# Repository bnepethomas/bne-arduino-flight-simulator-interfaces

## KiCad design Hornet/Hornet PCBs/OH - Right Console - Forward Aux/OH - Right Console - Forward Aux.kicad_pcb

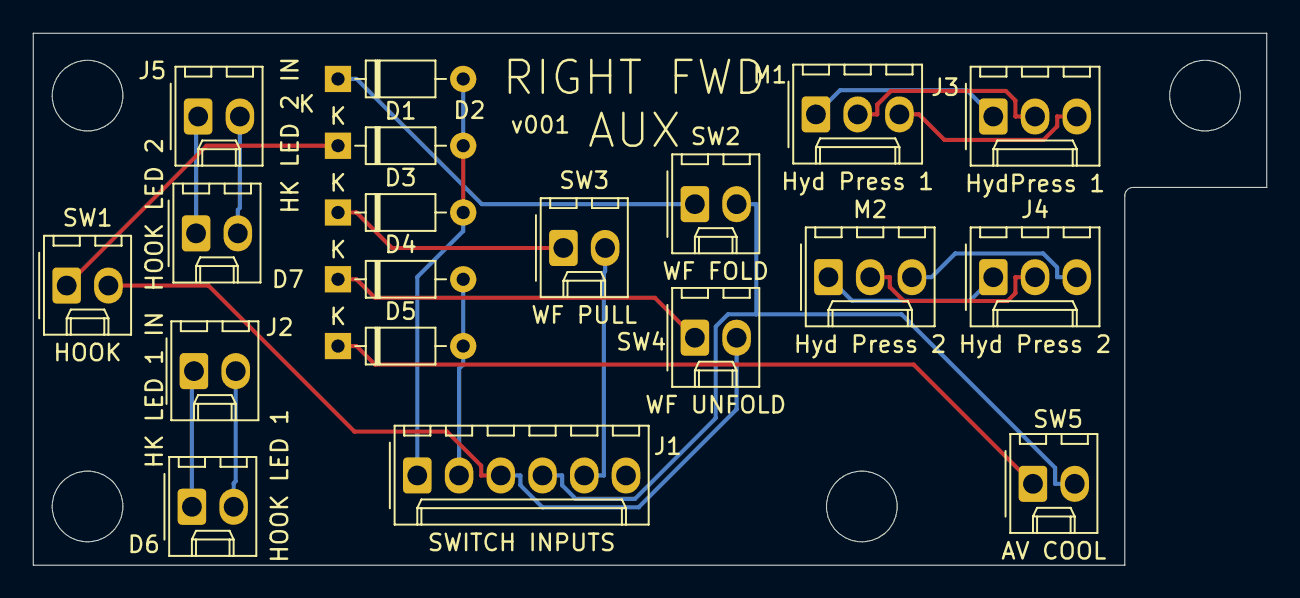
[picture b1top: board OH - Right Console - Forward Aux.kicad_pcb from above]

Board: 2 copper layers, 75.1 x 32.4 mm, 23 parts (0 on the bottom side), 20 nets.

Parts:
D1, D2, D3, D4, D5: D; D_Signal_P7.62mm_Horizontal
D6: HOOK LED 1; Molex_1x02_P2.54mm_Vertical
D7: HOOK LED 2; Molex_1x02_P2.54mm_Vertical
H1, H2, H3, H4: MountingHole; MountingHole_4.3mm_M4
J1: SWITCH INPUTS; Molex_1x06_P2.54mm_Vertical
J2: HK LED 1 IN; Molex_1x02_P2.54mm_Vertical
J3: HydPress 1; Molex_1x03_P2.54mm_Vertical
J4: Hyd Press 2; Molex_1x03_P2.54mm_Vertical
J5: HK LED 2 IN; Molex_1x02_P2.54mm_Vertical
M1: Hyd Press 1; Molex_1x03_P2.54mm_Vertical
M2: Hyd Press 2; Molex_1x03_P2.54mm_Vertical
SW1: HOOK; Molex_1x02_P2.54mm_Vertical
SW2: WF FOLD; Molex_1x02_P2.54mm_Vertical
SW3: WF PULL; Molex_1x02_P2.54mm_Vertical
SW4: WF UNFOLD; Molex_1x02_P2.54mm_Vertical
SW5: AV COOL; Molex_1x02_P2.54mm_Vertical

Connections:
/COL1: D1.2, D2.2, D3.2, J1.1
/COL2: D4.2, D5.2, J1.2
/ROW1: J1.3, SW1.2, SW4.2
/ROW2: J1.4, SW2.2, SW5.2
/ROW3: J1.5, SW3.2
unnamed: D1.1, SW1.1
unnamed: D2.1, SW2.1
unnamed: D3.1, SW3.1
unnamed: D4.1, SW4.1
unnamed: D5.1, SW5.1
unnamed: D6.1, J2.1
unnamed: D6.2, J2.2
unnamed: D7.1, J5.1
unnamed: D7.2, J5.2
unnamed: J3.1, M1.1
unnamed: J3.2, M1.2
unnamed: J3.3, M1.3
unnamed: J4.1, M2.1
unnamed: J4.2, M2.2
unnamed: J4.3, M2.3

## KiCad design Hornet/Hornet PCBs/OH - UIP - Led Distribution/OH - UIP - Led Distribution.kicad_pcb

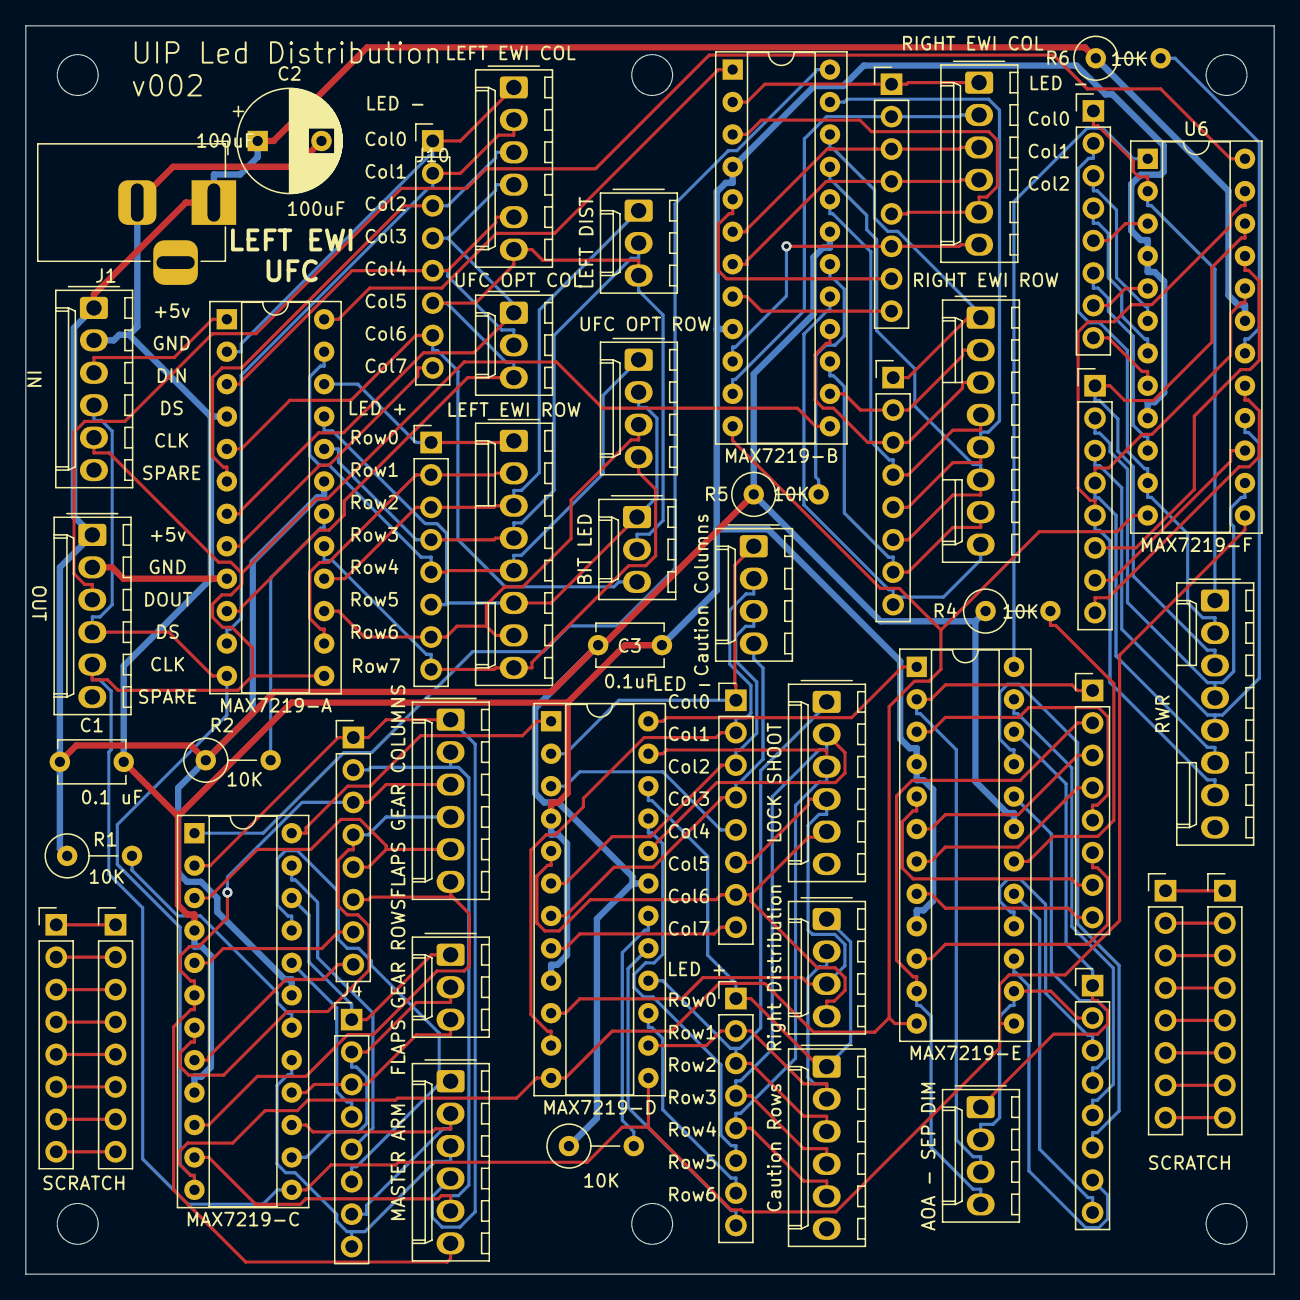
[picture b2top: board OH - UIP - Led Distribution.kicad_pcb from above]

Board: 2 copper layers, 97.8 x 97.8 mm, 57 parts (0 on the bottom side), 129 nets.

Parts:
C1, C3: 0.1uF; C_Disc_D5.1mm_W3.2mm_P5.00mm
C2: 100uF; CP_Radial_D8.0mm_P5.00mm
H1, H2, H3, H4, H5, H6: MountingHole; MountingHole_3.2mm_M3
J1: Conn_01x02_Female; BarrelJack_Horizontal
J2, J3: Molex_1x06_P2.54mm_Vertical
J4, J5, J9, J10, J16, J17, J23, J24, J26, J27, J30, J31, J32, J33, J35, J36: PinHeader_1x08_P2.54mm_Vertical
J6: FLAPS GEAR COLUMNS; Molex_1x06_P2.54mm_Vertical
J7: FLAPS GEAR ROWS; Molex_1x03_P2.54mm_Vertical
J8: MASTER ARM; Molex_1x06_P2.54mm_Vertical
J11: LEFT EWI ROW; Molex_1x08_P2.54mm_Vertical
J12: LEFT EWI COL; Molex_1x06_P2.54mm_Vertical
J13: UFC OPT COL; Molex_1x03_P2.54mm_Vertical
J14: UFC OPT ROW; Molex_1x04_P2.54mm_Vertical
J15: BIT LED; Molex_1x03_P2.54mm_Vertical
J18: Right Distribution; Molex_1x04_P2.54mm_Vertical
J19: LOCK SHOOT; Molex_1x06_P2.54mm_Vertical
J20: Caution Columns; Molex_1x04_P2.54mm_Vertical
J21: Caution Rows; Molex_1x06_P2.54mm_Vertical
J22: LEFT DIST; Molex_1x03_P2.54mm_Vertical
J25: AOA - SEP DIM; Molex_1x04_P2.54mm_Vertical
J28: RIGHT EWI ROW; Molex_1x08_P2.54mm_Vertical
J29: RIGHT EWI COL; Molex_1x06_P2.54mm_Vertical
J34: RWR; Molex_1x08_P2.54mm_Vertical
R1, R2, R3, R4, R5, R6: 10K; R_Axial_DIN0309_L9.0mm_D3.2mm_P5.08mm_Vertical
U1: MAX7219-C; DIP-24_W7.62mm_Socket
U2: MAX7219-A; DIP-24_W7.62mm_Socket
U3: MAX7219-D; DIP-24_W7.62mm_Socket
U4: MAX7219-E; DIP-24_W7.62mm_Socket
U5: MAX7219-B; DIP-24_W7.62mm_Socket
U6: MAX7219-F; DIP-24_W7.62mm_Socket

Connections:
+5V: C1.1, C2.1, C3.1, J1.1, J2.1, J3.1, R1.1, R2.1, R3.1, R4.1, R5.1, R6.1, U1.19, U2.19, U3.19, U4.19, U5.19, U6.19
/A-DOUT-B-DIN: U2.24, U5.1
/ACol0: J10.1, J12.1, U2.2
/ACol1: J10.2, J12.2, U2.11
/ACol2: J10.3, J12.3, U2.6
/ACol3: J10.4, J12.4, J13.1, U2.7
/ACol4: J10.5, J12.5, J13.2, U2.3
/ACol5: J10.6, J12.6, J13.3, J15.2, J22.3, U2.10
/ACol6: J10.7, J15.3, U2.5
/ACol7: J10.8, U2.8
/ARow0: J9.1, J11.1, U2.22
/ARow1: J9.2, J11.2, U2.14
/ARow2: J9.3, J11.3, J22.1, U2.16
/ARow3: J9.4, J11.4, J22.2, U2.20
/ARow4: J9.5, J11.5, J14.1, U2.23
/ARow5: J9.6, J11.6, J14.2, J15.1, U2.21
/ARow6: J9.7, J11.7, J14.3, U2.15
/ARow7: J9.8, J11.8, J14.4, U2.17
/B-DOUT-C-DIN: U1.1, U5.24
/BCol0: J27.1, J29.1, U5.2
/BCol1: J27.2, J29.2, U5.11
/BCol2: J27.3, J29.3, U5.6
/BCol3: J27.4, J29.4, U5.7
/BCol4: J27.5, J29.5, U5.3
/BCol5: J27.6, J29.6, U5.10
/BCol6: J27.7, U5.5
/BCol7: J27.8, U5.8
/BRow0: J26.1, J28.1, U5.22
/BRow1: J26.2, J28.2, U5.14
/BRow2: J26.3, J28.3, U5.16
/BRow3: J26.4, J28.4, U5.20
/BRow4: J26.5, J28.5, U5.23
/BRow5: J26.6, J28.6, U5.21
/BRow6: J26.7, J28.7, U5.15
/BRow7: J26.8, J28.8, U5.17
/C-DOUT-D-DIN: U1.24, U3.1
/CCol0: J5.1, J6.1, J8.4, U1.2
/CCol1: J5.2, J6.2, J8.5, U1.11
/CCol2: J5.3, J6.3, J8.6, U1.6
/CCol3: J5.4, J6.4, U1.7
/CCol4: J5.5, J6.5, U1.3
/CCol5: J5.6, J6.6, U1.10
/CCol6: J5.7, U1.5
/CCol7: J5.8, U1.8
/CLK: J2.5, J3.5, U1.13, U2.13, U3.13, U4.13, U5.13, U6.13
/CRow0: J4.1, J7.1, U1.22
/CRow1: J4.2, J7.2, U1.14
/CRow2: J4.3, J7.3, U1.16
/CRow3: J4.4, U1.20
/CRow4: J4.5, U1.23
/CRow5: J4.6, J8.1, U1.21
/CRow6: J4.7, J8.2, U1.15
/CRow7: J4.8, J8.3, U1.17
/D-DOUT-E-DIN: U3.24, U4.1
/DCol0: J16.1, J20.1, U3.2
/DCol1: J16.2, J20.2, U3.11
/DCol2: J16.3, J20.3, U3.6
/DCol3: J16.4, J20.4, U3.7
/DCol4: J16.5, U3.3
/DCol5: J16.6, J18.3, J19.4, U3.10
/DCol6: J16.7, J18.4, J19.5, U3.5
/DCol7: J16.8, U3.8
/DIN: J2.3, U2.1
/DOUT: J3.3, U6.24
/DRow0: J17.1, J18.1, J21.1, U3.22
/DRow1: J17.2, J18.2, J21.2, U3.14
/DRow2: J17.3, J19.1, J21.3, U3.16
/DRow3: J17.4, J19.2, J21.4, U3.20
/DRow4: J17.5, J19.3, J21.5, U3.23
/DRow5: J17.6, U3.21
/DRow6: J17.7, U3.15
/DRow7: J17.8, U3.17
/E-DOUT-F-DIN: U4.24, U6.1
/ECol0: J23.1, J25.3, U4.2
/ECol1: J23.2, J25.4, U4.11
/ECol2: J23.3, U4.6
/ECol3: J23.4, U4.7
/ECol4: J23.5, U4.3
/ECol5: J23.6, U4.10
/ECol6: J23.7, U4.5
/ECol7: J23.8, U4.8
/ERow0: J24.1, J25.1, U4.22
/ERow1: J24.2, J25.2, U4.14
/ERow2: J24.3, U4.16
/ERow3: J24.4, U4.20
/ERow4: J24.5, U4.23
/ERow5: J24.6, U4.21
/ERow6: J24.7, U4.15
/ERow7: J24.8, U4.17
/FCol0: J32.1, J34.1, U6.2
/FCol1: J32.2, J34.2, U6.11
/FCol2: J32.3, U6.6
/FCol3: J32.4, U6.7
/FCol4: J32.5, U6.3
/FCol5: J32.6, U6.10
/FCol6: J32.7, U6.5
/FCol7: J32.8, U6.8
/FRow0: J33.1, J34.3, U6.22
/FRow1: J33.2, J34.4, U6.14
/FRow2: J33.3, J34.5, U6.16
/FRow3: J33.4, J34.6, U6.20
/FRow4: J33.5, J34.7, U6.23
/FRow5: J33.6, U6.21
/FRow6: J33.7, U6.15
/FRow7: J33.8, U6.17
/LOAD: J2.4, J3.4, U1.12, U2.12, U3.12, U4.12, U5.12, U6.12
GND: C1.2, C2.2, C3.2, J1.2, J2.2, J3.2, U1.4, U1.9, U2.4, U2.9, U3.4, U3.9, U4.4, U4.9, U5.4, U5.9, U6.4, U6.9
unnamed: J30.1, J31.1
unnamed: J30.2, J31.2
unnamed: J30.3, J31.3
unnamed: J30.4, J31.4
unnamed: J30.5, J31.5
unnamed: J30.6, J31.6
unnamed: J30.7, J31.7
unnamed: J30.8, J31.8
unnamed: J35.1, J36.1
unnamed: J35.2, J36.2
unnamed: J35.3, J36.3
unnamed: J35.4, J36.4
unnamed: J35.5, J36.5
unnamed: J35.6, J36.6
unnamed: J35.7, J36.7
unnamed: J35.8, J36.8
unnamed: R1.2, U1.18
unnamed: R2.2, U2.18
unnamed: R3.2, U3.18
unnamed: R4.2, U4.18
unnamed: R5.2, U5.18
unnamed: R6.2, U6.18

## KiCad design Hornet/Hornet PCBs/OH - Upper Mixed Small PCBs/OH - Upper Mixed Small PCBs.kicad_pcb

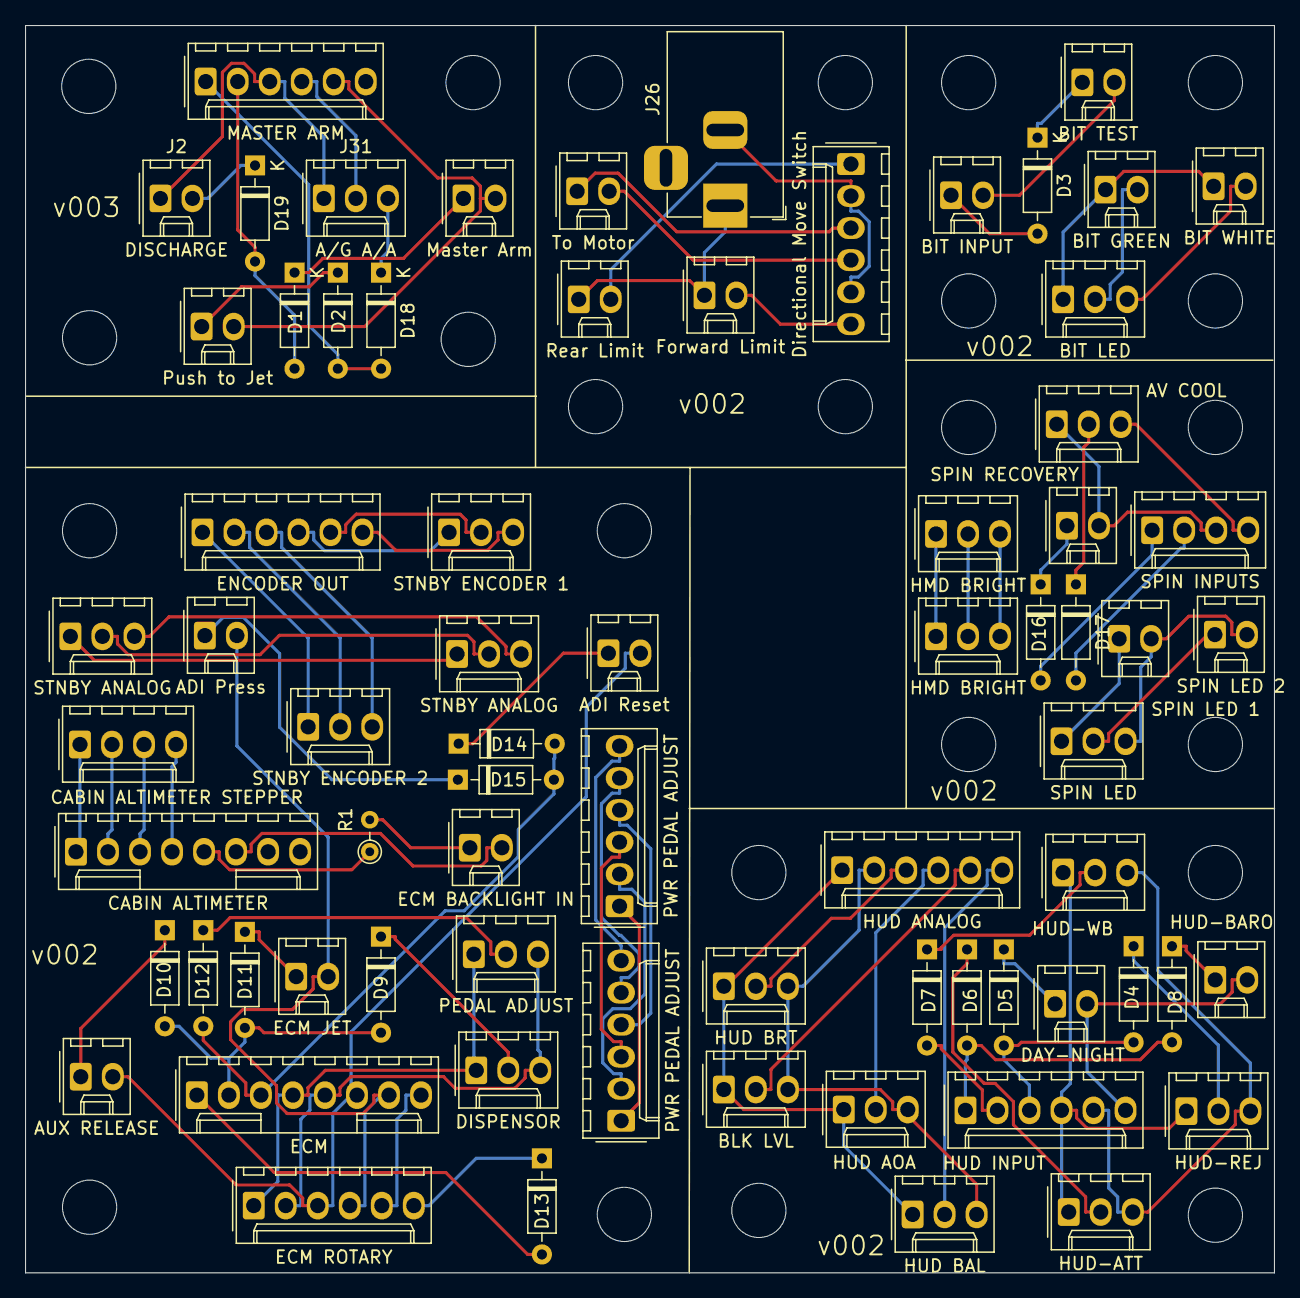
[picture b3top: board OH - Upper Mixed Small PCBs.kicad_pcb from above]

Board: 2 copper layers, 99.1 x 98.9 mm, 96 parts (0 on the bottom side), 87 nets.

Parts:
D1, D2, D3, D4, D5, D6, D7, D8, D9, D10, D11, D12, D13, D14, D15, D16, D17: D; D_Signal_P7.62mm_Horizontal
D18, D19: D; D_DO-35_SOD27_P7.62mm_Horizontal
H1, H5, H8, H11, H12, H14, H15, H16, H17, H18, H19, H20, H21, H22, H23, H24, H25, H26, H27, H28, H29, H30, H31, H32: MountingHole; MountingHole_4.3mm_M4
J1: HUD ANALOG; Molex_1x06_P2.54mm_Vertical
J2: DISCHARGE; Molex_KK-254_AE-6410-02A_1x02_P2.54mm_Vertical
J4: BIT GREEN; Molex_1x02_P2.54mm_Vertical
J5: BIT WHITE; Molex_1x02_P2.54mm_Vertical
J6: MASTER ARM; Molex_1x06_P2.54mm_Vertical
J7: BIT INPUT; Molex_1x02_P2.54mm_Vertical
J8: BIT LED; Molex_1x03_P2.54mm_Vertical
J9, J13: PWR PEDAL ADJUST; Molex_1x06_P2.54mm_Vertical
J10: HUD INPUT; Molex_1x06_P2.54mm_Vertical
J11: ECM BACKLIGHT IN; Molex_1x02_P2.54mm_Vertical
J12: CABIN ALTIMETER STEPPER; Molex_1x04_P2.54mm_Vertical
J14: CABIN ALTIMETER; Molex_1x08_P2.54mm_Vertical
J15, J19: STNBY ANALOG; Molex_1x03_P2.54mm_Vertical
J16: ECM; Molex_1x08_P2.54mm_Vertical
J17: STNBY ENCODER 1; Molex_1x03_P2.54mm_Vertical
J18: STNBY ENCODER 2; Molex_1x03_P2.54mm_Vertical
J20: ENCODER OUT; Molex_1x06_P2.54mm_Vertical
J21: SPIN INPUTS; Molex_1x04_P2.54mm_Vertical
J22: SPIN LED; Molex_1x03_P2.54mm_Vertical
J23: HMD BRIGHT; Molex_1x03_P2.54mm_Vertical
J24: SPIN LED 1; Molex_1x02_P2.54mm_Vertical
J25: SPIN LED 2; Molex_1x02_P2.54mm_Vertical
J26: PEDAL POWER IN; BarrelJack_Horizontal
J27: To Motor; Molex_1x02_P2.54mm_Vertical
J28: Rear Limit; Molex_1x02_P2.54mm_Vertical
J29: Directional Move Switch; Molex_1x06_P2.54mm_Vertical
J30: Forward Limit; Molex_1x02_P2.54mm_Vertical
J31: A/G A/A; Molex_KK-254_AE-6410-03A_1x03_P2.54mm_Vertical
R1: 1K; PT_R_Axial_DIN0204_L3.6mm_D1.6mm_P2.54mm_Vertical
RV1: HUD BRT; Molex_1x03_P2.54mm_Vertical
RV2: HUD AOA; Molex_1x03_P2.54mm_Vertical
RV3: BLK LVL; Molex_1x03_P2.54mm_Vertical
RV4: HUD BAL; Molex_1x03_P2.54mm_Vertical
RV5: HMD BRIGHT; Molex_1x03_P2.54mm_Vertical
SW1: BIT TEST; Molex_1x02_P2.54mm_Vertical
SW2: Push to Jet; Molex_1x02_P2.54mm_Vertical
SW3: Master Arm; Molex_1x02_P2.54mm_Vertical
SW4: HUD-REJ; Molex_1x03_P2.54mm_Vertical
SW5: DAY-NIGHT; Molex_1x02_P2.54mm_Vertical
SW6: HUD-WB; Molex_1x03_P2.54mm_Vertical
SW7: HUD-BARO; Molex_1x02_P2.54mm_Vertical
SW8: HUD-ATT; Molex_1x03_P2.54mm_Vertical
SW9: DISPENSOR; Molex_1x03_P2.54mm_Vertical
SW10: AUX RELEASE; Molex_1x02_P2.54mm_Vertical
SW11: ECM JET; Molex_1x02_P2.54mm_Vertical
SW12: PEDAL ADJUST; Molex_1x03_P2.54mm_Vertical
SW13: ECM ROTARY; Molex_1x06_P2.54mm_Vertical
SW14: ADI Reset; Molex_1x02_P2.54mm_Vertical
SW15: ADI Press; Molex_1x02_P2.54mm_Vertical
SW16: AV COOL; Molex_1x03_P2.54mm_Vertical
SW17: SPIN RECOVERY; Molex_1x02_P2.54mm_Vertical

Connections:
+12V: J26.1, J28.1, J30.1
/ARM-ROW3: J6.5, SW2.2, SW3.2 (B)
/BIT-COL: D3.2 (A), J7.1
/BIT-LED-COL-1: J4.2, J8.2
/BIT-LED-COL-2: J5.2, J8.3
/BIT-LED-ROW-1: J4.1, J5.1, J8.1
/BIT-ROW: J7.2, SW1.2
/BLK-LVL: J1.5, RV3.2
/ECM-COL-1: D13.2 (A), J16.1
/ECM-COL-2: D9.2 (A), D10.2 (A), D11.2 (A), J16.2
/ECM-COL-3: D12.2 (A), D14.2 (A), D15.2 (A), J16.3
/ECM-ROW-1: J16.4, SW9.1, SW12.1, SW13.1
/ECM-ROW-2: J16.5, SW9.3, SW12.3, SW13.2
/ECM-ROW-3: J16.6, SW10.2 (B), SW13.3, SW14.2
/ECM-ROW-4: J16.7, SW11.2, SW13.4, SW15.2
/ECM-ROW-5: J16.8, SW13.5
/HUD-A0A: J1.4, RV2.2
/HUD-ANA+5V: J1.1, RV1.1, RV2.1, RV3.1, RV4.1
/HUD-ANA-GND: J1.2, RV1.3, RV2.3, RV3.3, RV4.3
/HUD-BAL: J1.6, RV4.2
/HUD-BRT: J1.3, RV1.2
/HUD-COL-1: D6.2 (A), D8.2 (A), J10.1
/HUD-COL-2: D7.2 (A), J10.2
/HUD-COL-3: D4.2 (A), D5.2 (A), J10.3
/HUD-ROW-1: J10.4, SW4.1, SW6.1, SW8.1
/HUD-ROW-2: J10.5, SW4.3, SW6.3, SW8.3
/HUD-ROW-3: J10.6, SW5.2 (B), SW7.2 (B)
/PCB-COL-1: D2.2 (A), D18.2 (A), J6.1
/PCB-COL-2: D1.2 (A), D19.2 (A), J6.2
/PCB-ROW-1: J2.1, J6.3, J31.1
/PCB-ROW-2: J6.4, J31.2
/SPIN-COL1: D16.2 (A), J21.1
/SPIN-COL2: D17.2 (A), J21.2
/SPIN-LED-ANNODE-1: J22.1, J24.1
/SPIN-LED-ANNODE-2: J22.2, J25.1
/SPIN-LED-CATHODE: J22.3, J24.2, J25.2
/SPIN-ROW1: J21.3, SW16.1, SW17.2 (B)
/SPIN-ROW2: J21.4, SW16.3
GND: J26.2, J29.2, J29.5
unnamed: D1.1 (K), SW3.1 (A)
unnamed: D2.1 (K), SW2.1
unnamed: D3.1 (K), SW1.1
unnamed: D4.1 (K), SW4.2
unnamed: D5.1 (K), SW5.1 (A)
unnamed: D6.1 (K), SW8.2
unnamed: D7.1 (K), SW6.2
unnamed: D8.1 (K), SW7.1 (A)
unnamed: D9.1 (K), SW9.2
unnamed: D10.1 (K), SW10.1 (A)
unnamed: D11.1 (K), SW11.1
unnamed: D12.1 (K), SW12.2
unnamed: D13.1 (K), SW13.6
unnamed: D14.1 (K), SW14.1
unnamed: D15.1 (K), SW15.1
unnamed: D16.1 (K), SW17.1 (A)
unnamed: D17.1 (K), SW16.2
unnamed: D18.1 (K), J31.3
unnamed: D19.1 (K), J2.2
unnamed: J11.1, R1.2
unnamed: J11.2, J14.6
unnamed: J12.1, J14.1
unnamed: J12.2, J14.2
unnamed: J12.3, J14.3
unnamed: J12.4, J14.4
unnamed: J9.1, J13.1
unnamed: J9.2, J13.2
unnamed: J9.3, J13.3
unnamed: J9.4, J13.4
unnamed: J9.5, J13.5
unnamed: J9.6, J13.6
unnamed: J14.5, R1.1
unnamed: J15.1, J19.1
unnamed: J15.2, J19.2
unnamed: J15.3, J19.3
unnamed: J17.1, J20.4
unnamed: J17.2, J20.5
unnamed: J17.3, J20.6
unnamed: J18.1, J20.1
unnamed: J18.2, J20.2
unnamed: J18.3, J20.3
unnamed: J23.1, RV5.1
unnamed: J23.2, RV5.2
unnamed: J23.3, RV5.3
unnamed: J27.1, J29.3
unnamed: J27.2, J29.4
unnamed: J28.2, J29.1
unnamed: J29.6, J30.2

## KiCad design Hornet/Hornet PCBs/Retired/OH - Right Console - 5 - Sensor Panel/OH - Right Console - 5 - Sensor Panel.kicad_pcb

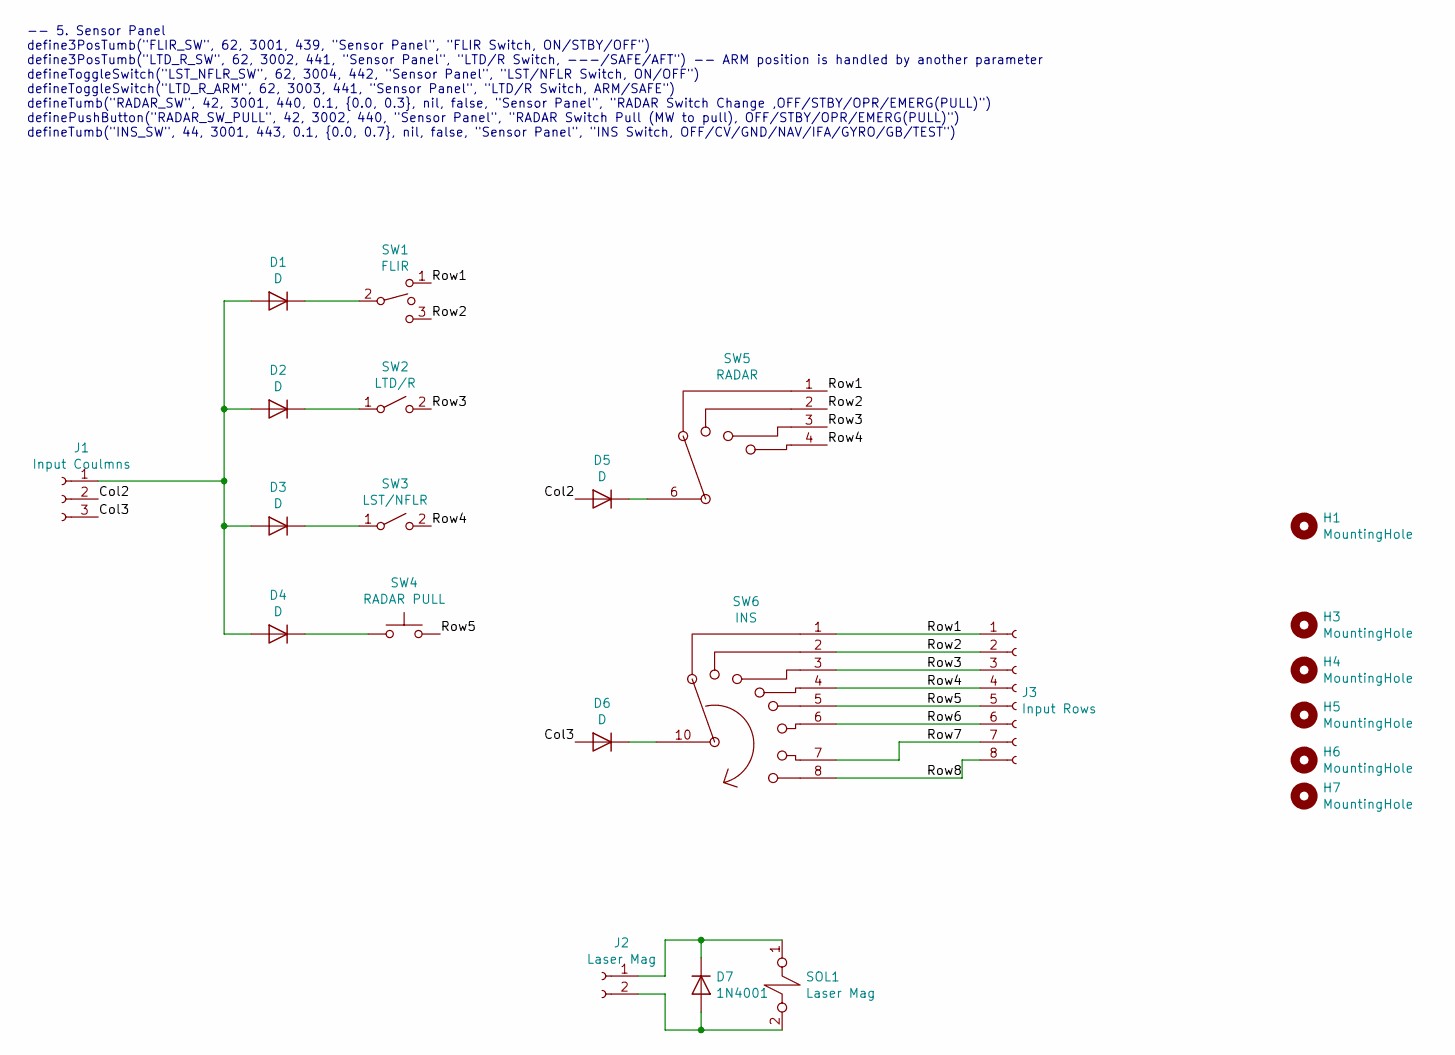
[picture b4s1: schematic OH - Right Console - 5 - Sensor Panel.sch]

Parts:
D1, D2, D3, D4, D5, D6: D; D_Signal_P7.62mm_Horizontal
D7: 1N4001; D_DO-41_SOD81_P10.16mm_Horizontal
H1, H3, H4, H5, H6, H7: MountingHole; MountingHole_3.2mm_M3
J1: Input Coulmns; Molex_1x03_P2.54mm_Vertical
J2: Laser Mag; Molex_1x02_P2.54mm_Vertical
J3: Input Rows; Molex_1x08_P2.54mm_Vertical
SOL1: Laser Mag; Molex_1x02_P2.54mm_Vertical
SW1: FLIR; Molex_1x03_P2.54mm_Vertical
SW2: LTD/R; Molex_1x02_P2.54mm_Vertical
SW3: LST/NFLR; Molex_1x02_P2.54mm_Vertical
SW4: RADAR PULL; Molex_1x02_P2.54mm_Vertical
SW5: RADAR; Molex_1x06_P2.54mm_Vertical
SW6: INS; Molex_1x10_P2.54mm_Vertical

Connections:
/Col2: D5.2 (A), J1.2
/Col3: D6.2 (A), J1.3
/Row1: J3.1, SW1.1, SW5.1, SW6.1
/Row2: J3.2, SW1.3, SW5.2, SW6.2
/Row3: J3.3, SW2.2 (B), SW5.3, SW6.3
/Row4: J3.4, SW3.2 (B), SW5.4, SW6.4
/Row5: J3.5, SW4.2, SW6.5
/Row6: J3.6, SW6.6
/Row7: J3.7, SW6.7
/Row8: J3.8, SW6.8
unnamed: D1.1 (K), SW1.2
unnamed: D1.2 (A), D2.2 (A), D3.2 (A), D4.2 (A), J1.1
unnamed: D2.1 (K), SW2.1 (A)
unnamed: D3.1 (K), SW3.1 (A)
unnamed: D4.1 (K), SW4.1
unnamed: D5.1 (K), SW5.6 (COM)
unnamed: D6.1 (K), SW6.10
unnamed: D7.1 (K), J2.1, SOL1.1
unnamed: D7.2 (A), J2.2, SOL1.2

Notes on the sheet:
-- 5. Sensor Panel define3PosTumb("FLIR_SW", 62, 3001, 439, "Sensor Panel", "FLIR Switch, ON/STBY/OFF") define3PosTumb("LTD_R_SW", 62, 3002, 441, "Sensor Panel", "LTD/R Switch, ---/SAFE/AFT") -- ARM position is handled by another parameter defineToggleSwitch("LST_NFLR_SW", 62, 3004, 442, "Sensor Pa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

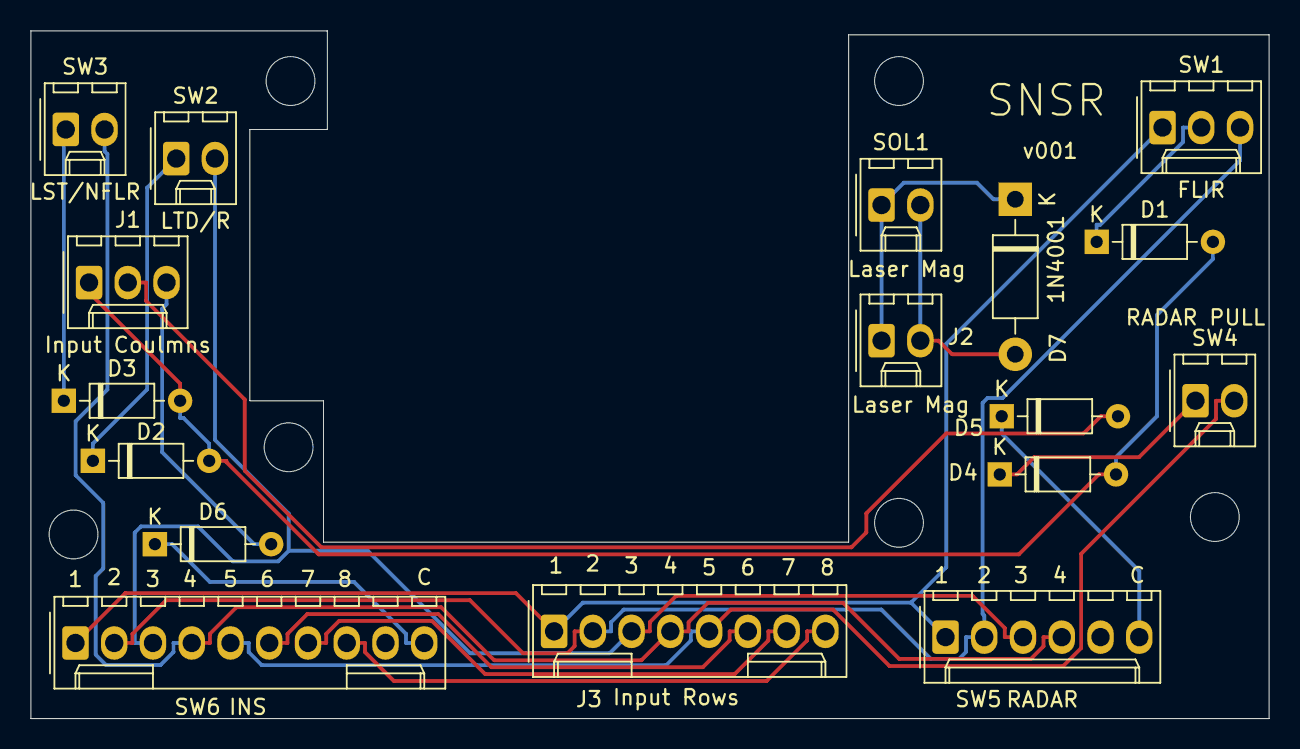
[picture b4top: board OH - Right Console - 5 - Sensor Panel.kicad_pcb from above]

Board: 2 copper layers, 81.2 x 45.1 mm, 23 parts (0 on the bottom side), 19 nets.

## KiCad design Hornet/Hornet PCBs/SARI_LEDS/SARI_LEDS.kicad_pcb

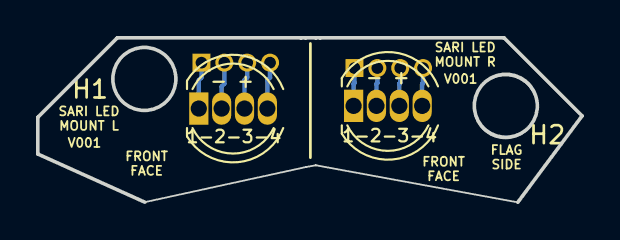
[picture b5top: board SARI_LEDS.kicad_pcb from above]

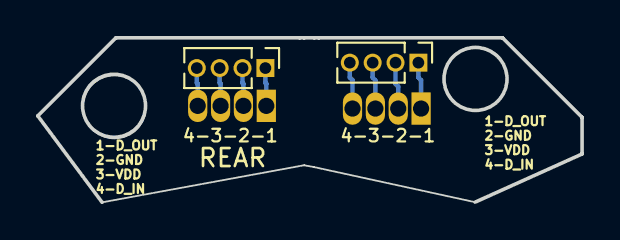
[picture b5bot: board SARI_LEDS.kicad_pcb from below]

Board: 2 copper layers, 30.2 x 9.1 mm, 6 parts (2 on the bottom side), 8 nets.

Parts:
D1, D2: NeoPixel_THT; LED_D5.0mm-4_RGB
H1, H2: MountingHole; MountingHole_3.5mm
J1, J2: BL OUT; PinHeader_1x04_P1.27mm_Vertical

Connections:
/DATA_IN-L: D1.4 (DIN), J1.4
/DATA_IN-R: D2.4 (DIN), J2.4
/DATA_OUT-L: D1.1 (DOUT), J1.1
/DATA_OUT-R: D2.1 (DOUT), J2.1
/GND_L: D1.2 (GND), J1.2
/GND_R: D2.2 (GND), J2.2
/VDD_L: D1.3 (VDD), J1.3
/VDD_R: D2.3 (VDD), J2.3

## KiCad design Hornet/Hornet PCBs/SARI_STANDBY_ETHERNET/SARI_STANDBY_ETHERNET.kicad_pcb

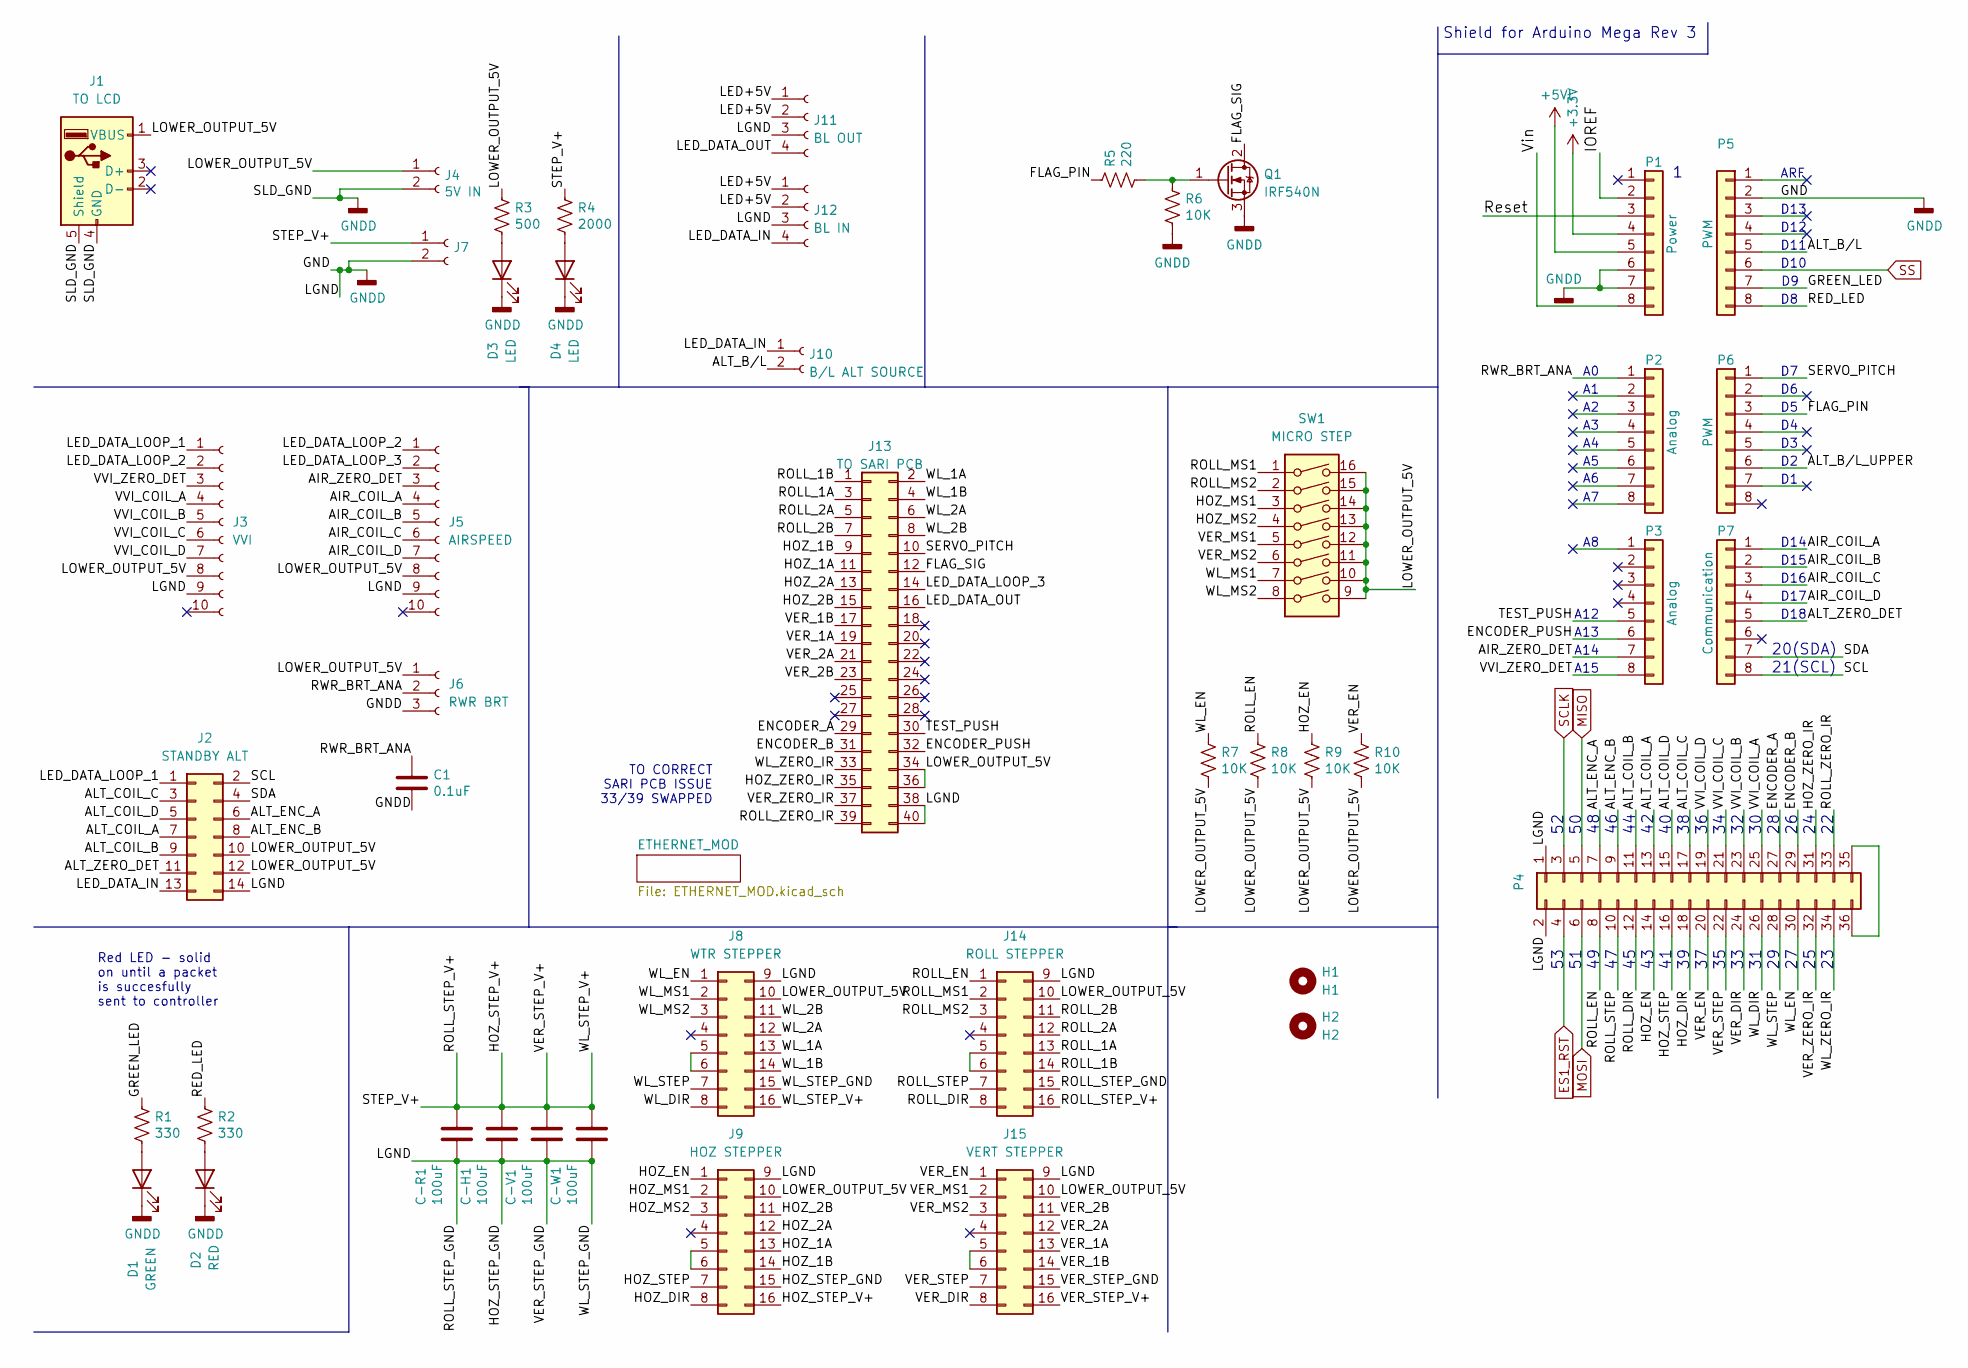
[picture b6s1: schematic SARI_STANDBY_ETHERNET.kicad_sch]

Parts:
C1: 0.1uF; C_Disc_D6.0mm_W2.5mm_P5.00mm
C-H1: 100uF; C_Radial_D8.0mm_H7.0mm_P3.50mm
C-R1: 100uF; C_Radial_D8.0mm_H7.0mm_P3.50mm
C-V1: 100uF; C_Radial_D8.0mm_H7.0mm_P3.50mm
C-W1: 100uF; C_Radial_D8.0mm_H7.0mm_P3.50mm
D1: GREEN; LED_D3.0mm
D2: RED; LED_D3.0mm
D3, D4: LED; LED_D3.0mm
H1: H1; MountingHole_2.5mm
H2: H2; MountingHole_2.5mm
J1: TO LCD; USB_A_Molex_67643_Horizontal
J2: STANDBY ALT; IDC-Header_2x07_P2.54mm_Vertical
J3: VVI; JST_XH_B10B-XH-A_1x10_P2.50mm_Vertical
J4: 5V IN; BarrelJack_Horizontal
J5: AIRSPEED; JST_XH_B10B-XH-A_1x10_P2.50mm_Vertical
J6: RWR BRT; JST_XH_B3B-XH-A_1x03_P2.50mm_Vertical
J7: STEPPER IN 12-20VDC; BarrelJack_Horizontal
J8: WTR STEPPER; Pololu_Breakout-16_15.2x20.3mm
J9: HOZ STEPPER; Pololu_Breakout-16_15.2x20.3mm
J10: B/L ALT SOURCE; PinHeader_1x02_P2.54mm_Vertical
J11: BL OUT; Molex_Mini-Fit_Jr_5566-04A_2x02_P4.20mm_Vertical
J12: BL IN; Molex_Mini-Fit_Jr_5566-04A_2x02_P4.20mm_Vertical
J13: TO SARI PCB; IDC-Header_2x20_P2.54mm_Vertical
J14: ROLL STEPPER; Pololu_Breakout-16_15.2x20.3mm
J15: VERT STEPPER; Pololu_Breakout-16_15.2x20.3mm
P1: Power; Socket_Strip_Arduino_1x08
P2, P3: Analog; Socket_Strip_Arduino_1x08
P4: Digital; Socket_Strip_Arduino_2x18
P5, P6: PWM; Socket_Strip_Arduino_1x08
P7: Communication; Socket_Strip_Arduino_1x08
Q1: IRF540N; TO-220-3_Vertical
R1: 330; R_Axial_DIN0204_L3.6mm_D1.6mm_P2.54mm_Vertical
R2: 330; PT_R_Axial_DIN0204_L3.6mm_D1.6mm_P2.54mm_Vertical
R3: 500; R_Axial_DIN0204_L3.6mm_D1.6mm_P2.54mm_Vertical
R4: 2000; R_Axial_DIN0204_L3.6mm_D1.6mm_P2.54mm_Vertical
R5: 220; R_Axial_DIN0204_L3.6mm_D1.6mm_P2.54mm_Vertical
R6, R7, R8, R9, R10: 10K; R_Axial_DIN0204_L3.6mm_D1.6mm_P2.54mm_Vertical
SW1: MICRO STEP; SW_DIP_SPSTx08_Slide_9.78x22.5mm_W7.62mm_P2.54mm

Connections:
+5VL: P1.5
/AIR_COIL_A: J5.4, P7.1
/AIR_COIL_B: J5.5, P7.2
/AIR_COIL_C: J5.6, P7.3
/AIR_COIL_D: J5.7, P7.4
/AIR_ZERO_DET: J5.3, P3.7
/ALT_B/L: J10.2, P5.5, P6.7
/ALT_B/L_UPPER: P6.6
/ALT_COIL_A: J2.7, P4.13
/ALT_COIL_B: J2.9, P4.11
/ALT_COIL_C: J2.3, P4.17
/ALT_COIL_D: J2.5, P4.15
/ALT_ENC_A: J2.6, P4.7
/ALT_ENC_B: J2.8, P4.9
/ALT_ZERO_DET: J2.11, P7.5
/ENCODER_A: J13.29, P4.27
/ENCODER_B: J13.31, P4.29
/ENCODER_PUSH: J13.32, P3.6
/FLAG_PIN: P6.3, R5.1
/FLAG_SIG: J13.12, Q1.2 (D)
/GREEN_LED: P5.7, R1.1
/HOZ_1A: J9.13, J13.11
/HOZ_1B: J9.14, J13.9
/HOZ_2A: J9.12, J13.13
/HOZ_2B: J9.11, J13.15
/HOZ_DIR: J9.8, P4.18
/HOZ_EN: J9.1, P4.14, R9.1
/HOZ_MS1: J9.2, SW1.3
/HOZ_MS2: J9.3, SW1.4
/HOZ_STEP: J9.7, P4.16
/HOZ_STEP_V+: C-H1.1, C-R1.1, C-V1.1, C-W1.1, J7.1, J8.16, J9.16, J14.16, J15.16, R4.1
/HOZ_ZERO_IR: J13.35, P4.31
/IOREF: P1.2
/LED+5V: J11.1, J11.2, J12.1, J12.2
/LED_DATA_IN: J2.13, J10.1, J12.4
/LED_DATA_LOOP_1: J2.1, J3.1
/LED_DATA_LOOP_2: J3.2, J5.1
/LED_DATA_LOOP_3: J5.2, J13.14
/LED_DATA_OUT: J11.4, J13.16
/LOWER_OUTPUT_5V: J1.1 (VBUS), J2.10, J2.12, J3.8, J4.1, J5.8, J6.1, J8.10, J9.10, J13.34, J13.36, J14.10, J15.10, R3.1, R7.2, R8.2, R9.2, R10.2, SW1.9, SW1.10, SW1.11, SW1.12, SW1.13, SW1.14, SW1.15, SW1.16
/RED_LED: P5.8, R2.1
/ROLL_1A: J13.3, J14.13
/ROLL_1B: J13.1, J14.14
/ROLL_2A: J13.5, J14.12
/ROLL_2B: J13.7, J14.11
/ROLL_DIR: J14.8, P4.12
/ROLL_EN: J14.1, P4.8, R8.1
/ROLL_MS1: J14.2, SW1.1
/ROLL_MS2: J14.3, SW1.2
/ROLL_STEP: J14.7, P4.10
/ROLL_ZERO_IR: J13.39, P4.33
/RWR_BRT_ANA: C1.1, J6.2, P2.1
/Reset: P1.3
/SCL: J2.2, P7.8
/SDA: J2.4, P7.7
/SERVO_PITCH: J13.10, P6.1
/TEST_PUSH: J13.30, P3.5
/VER_1A: J13.19, J15.13
/VER_1B: J13.17, J15.14
/VER_2A: J13.21, J15.12
/VER_2B: J13.23, J15.11
/VER_DIR: J15.8, P4.24
/VER_EN: J15.1, P4.20, R10.1
/VER_MS1: J15.2, SW1.5
/VER_MS2: J15.3, SW1.6
/VER_STEP: J15.7, P4.22
/VER_ZERO_IR: J13.37, P4.32
/VVI_COIL_A: J3.4, P4.25
/VVI_COIL_B: J3.5, P4.23
/VVI_COIL_C: J3.6, P4.21
/VVI_COIL_D: J3.7, P4.19
/VVI_ZERO_DET: J3.3, P3.8
/Vin: P1.8
/WL_1A: J8.13, J13.2
/WL_1B: J8.14, J13.4
/WL_2A: J8.12, J13.6
/WL_2B: J8.11, J13.8
/WL_DIR: J8.8, P4.26
/WL_EN: J8.1, P4.30, R7.1
/WL_MS1: J8.2, SW1.7
/WL_MS2: J8.3, SW1.8
/WL_STEP: J8.7, P4.28
/WL_ZERO_IR: J13.33, P4.34
ES1_RST: P4.4; also elsewhere on the board
MISO: P4.5; also elsewhere on the board
MOSI: P4.6; also elsewhere on the board
unnamed: D1.2 (A), R1.2
unnamed: D2.2 (A), R2.2
unnamed: D3.2 (A), R3.2
unnamed: D4.2 (A), R4.2
unnamed: J8.5, J8.6
unnamed: J9.5, J9.6
unnamed: J14.5, J14.6
unnamed: J15.5, J15.6
unnamed: P4.35, P4.36
unnamed: Q1.1 (G), R5.2, R6.1
SCLK: P4.3; also elsewhere on the board
SS: P5.6; also elsewhere on the board

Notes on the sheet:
A14
ARF
Shield for Arduino Mega Rev 3
D10
TO CORRECT SARI PCB ISSUE 33/39 SWAPPED
D13
Red LED - solid on until a packet is succesfully sent to controller
A13
A12
D14
A15
D15
D12
D17
D11
20(SDA)
21(SCL)
D16
D18

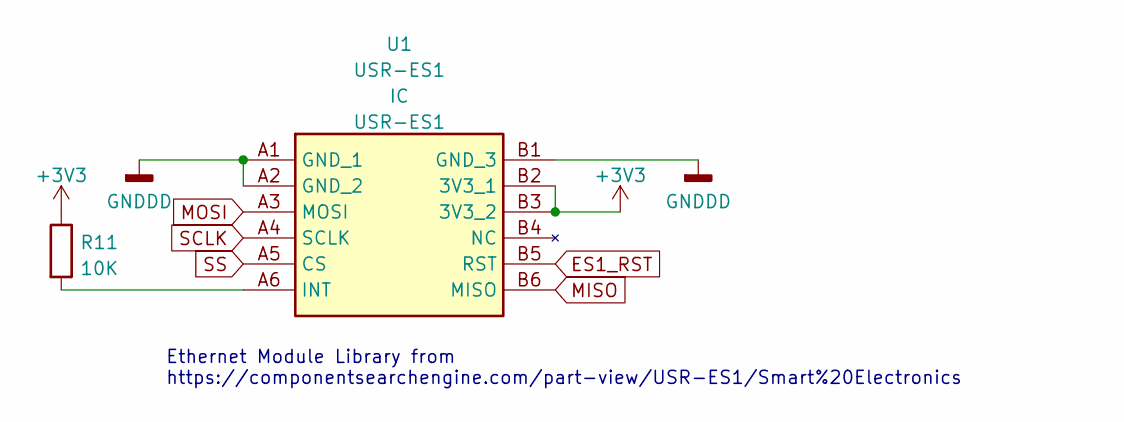
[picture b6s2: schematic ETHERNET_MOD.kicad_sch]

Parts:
R11: 10K; PT_R_Axial_DIN0204_L3.6mm_D1.6mm_P2.54mm_Vertical
U1: USR-ES1; USRES1; Manufacturer_Part_Number USR-ES1

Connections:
ES1_RST: U1.B5 (RST); also elsewhere on the board
MISO: U1.B6 (MISO); also elsewhere on the board
MOSI: U1.A3 (MOSI); also elsewhere on the board
unnamed: R11.2, U1.A6 (INT)
SCLK: U1.A4 (SCLK); also elsewhere on the board
SS: U1.A5 (CS); also elsewhere on the board

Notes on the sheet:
Ethernet Module Library from https://componentsearchengine.com/part-view/USR-ES1/Smart%20Electronics

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
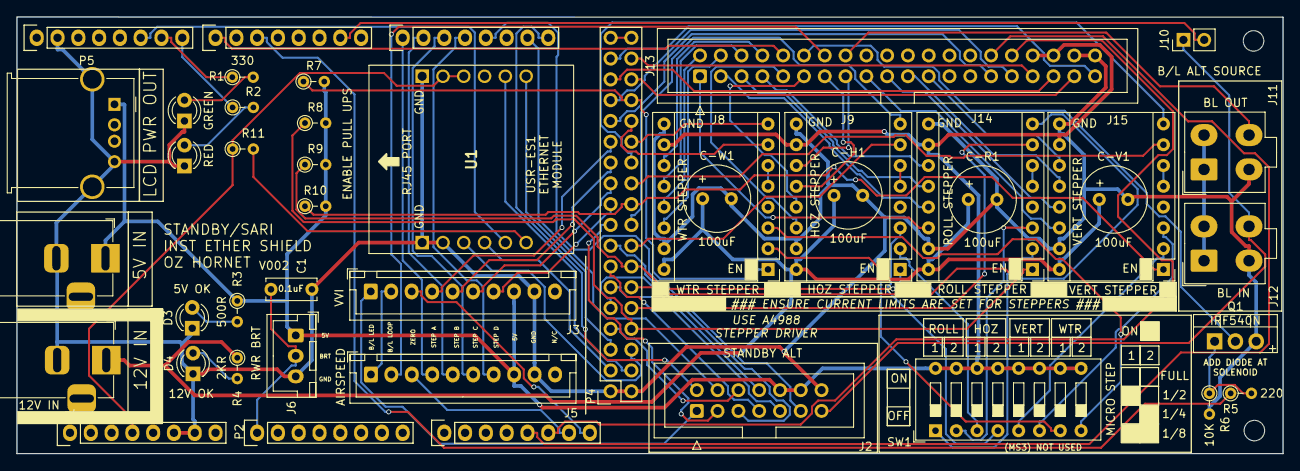
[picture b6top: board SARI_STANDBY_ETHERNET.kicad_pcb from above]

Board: 2 copper layers, 154.7 x 53.3 mm, 47 parts (0 on the bottom side), 96 nets.
